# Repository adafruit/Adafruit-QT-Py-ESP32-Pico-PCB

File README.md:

## Adafruit QT Py ESP32 Pico - WiFi Dev Board with STEMMA QT

<a href="http://www.adafruit.com/products/5395"><br/>
Click here to purchase one from the Adafruit shop</a>

PCB files for the Adafruit QT Py ESP32 Pico.

Format is EagleCAD schematic and board layout
* https://www.adafruit.com/product/5395

### Description

This dev board is like when you're watching a super-hero movie and the protagonist shows up in a totally amazing costume in the third act and you're like 'OMG! That's the hero and they're here to kick some serious butt!" but in this case its a microcontroller.

This QT Py board is a thumbnail-sized PCB that features the ESP32 Pico V3 02, an all-in-one chip that has an ESP32 chip with dual-core 240MHz Tensilica processor, WiFi and Bluetooth classic + BLE, adds a bunch of required passives and oscillator, 8 MB of Flash memory and 2 MB of PSRAM. We add a USB to serial converter chip, some more passives, an antenna, USB C, buttons, NeoPixel and QT connector to outfit this super-hero chip for any task you want to throw it at.

At the core of ESP32-PICO-V3-02 is the ESP32 (ECO V3) chip, which is a single 2.4 GHz Wi-Fi and Bluetooth combo chip designed with TSMC’s 40 nm low-power technology. ESP32-PICO-V3-02 integrates all peripheral components seamlessly, including a crystal oscillator, flash, PSRAM, filter capacitors, and RF matching links in one single package. This makes it perfect for stuffing into such a small space as the QT Py.

Please note the QT Py ESP32 Pico does not have native USB support - instead there's a USB to serial converter chip. This means it cannot act like a USB keyboard or mouse - but it does have BLE and BT classic so you could  wireless.

OLEDs! Inertial Measurement Units! Sensors a-plenty. All plug-and-play thanks to the innovative chainable design: SparkFun Qwiic-compatible STEMMA QT connectors for the I2C bus so you don't even need to solder! Just plug in a compatible cable and attach it to your MCU of choice, and you’re ready to load up some software and measure some light. Seeed Grove I2C boards will also work with this adapter cable.

Pinout and shape are Seeed Xiao compatible, with castellated pads. In addition to the QT connector, we also added an RGB NeoPixel (with controllable power pin to allow for ultra-low-power usage), a reset button (great for restarting your program or entering the bootloader), and a button on GPIO 0 for entering the ROM bootloader or for user input

Runs Arduino like a dream, or use the ESP IDF for more control over your projects.

* Same size, form-factor, and pin-out as Seeed Xiao
* USB Type C connector - If you have only Micro B cables, this adapter will come in handy!
* ESP32 V2 03 Dual Core 240MHz Xtensa processor - the ESP32 you know and love, with the latest engineering fixes. Massive user base and thousands of existing projects and libraries to use.
* WiFi, Bluetooth LE and Classic for any IoT project usage
* 8 MB Flash & 2 MB PSRAM
* USB to Serial converter built in with high speed UART for debugging and uploading.
* Can be used with Arduino IDE or MicroPython
* Built-in RGB NeoPixel LED with power control to reduce quiescent power in deep sleep
* Battery input pads on underside with diode protection for external battery packs up to 6V input
* 13 GPIO pins:
  * 11 on breakout pads, 2 more on QT connector
  * 10 x 12-bit analog inputs
  * Dual 8-bit analog output DACs on A0/A1
  * PWM outputs on any pin
  * Two I2C ports, one on the breakout pads, and another with STEMMA QT plug-n-play connector
  * Hardware UART in addition to the USB-serial UART
  * Hardware SPI on the high speed SPI peripheral pins
  * Hardware I2S on any pins
  * 8 x Capacitive Touch with no additional components required
* 3.3V regulator with 600mA peak output
* Light sleep at 4mA, deep sleep at ~70uA
* Reset switch for starting your project code over, boot 0 button for entering bootloader mode or for user reading
* Really really small

### License

Adafruit invests time and resources providing this open source design, please support Adafruit and open-source hardware by purchasing products from [Adafruit](https://www.adafruit.com)!

Designed by Limor Fried/Ladyada for Adafruit Industries.

Creative Commons Attribution/Share-Alike, all text above must be included in any redistribution. 
See license.txt for additional details.

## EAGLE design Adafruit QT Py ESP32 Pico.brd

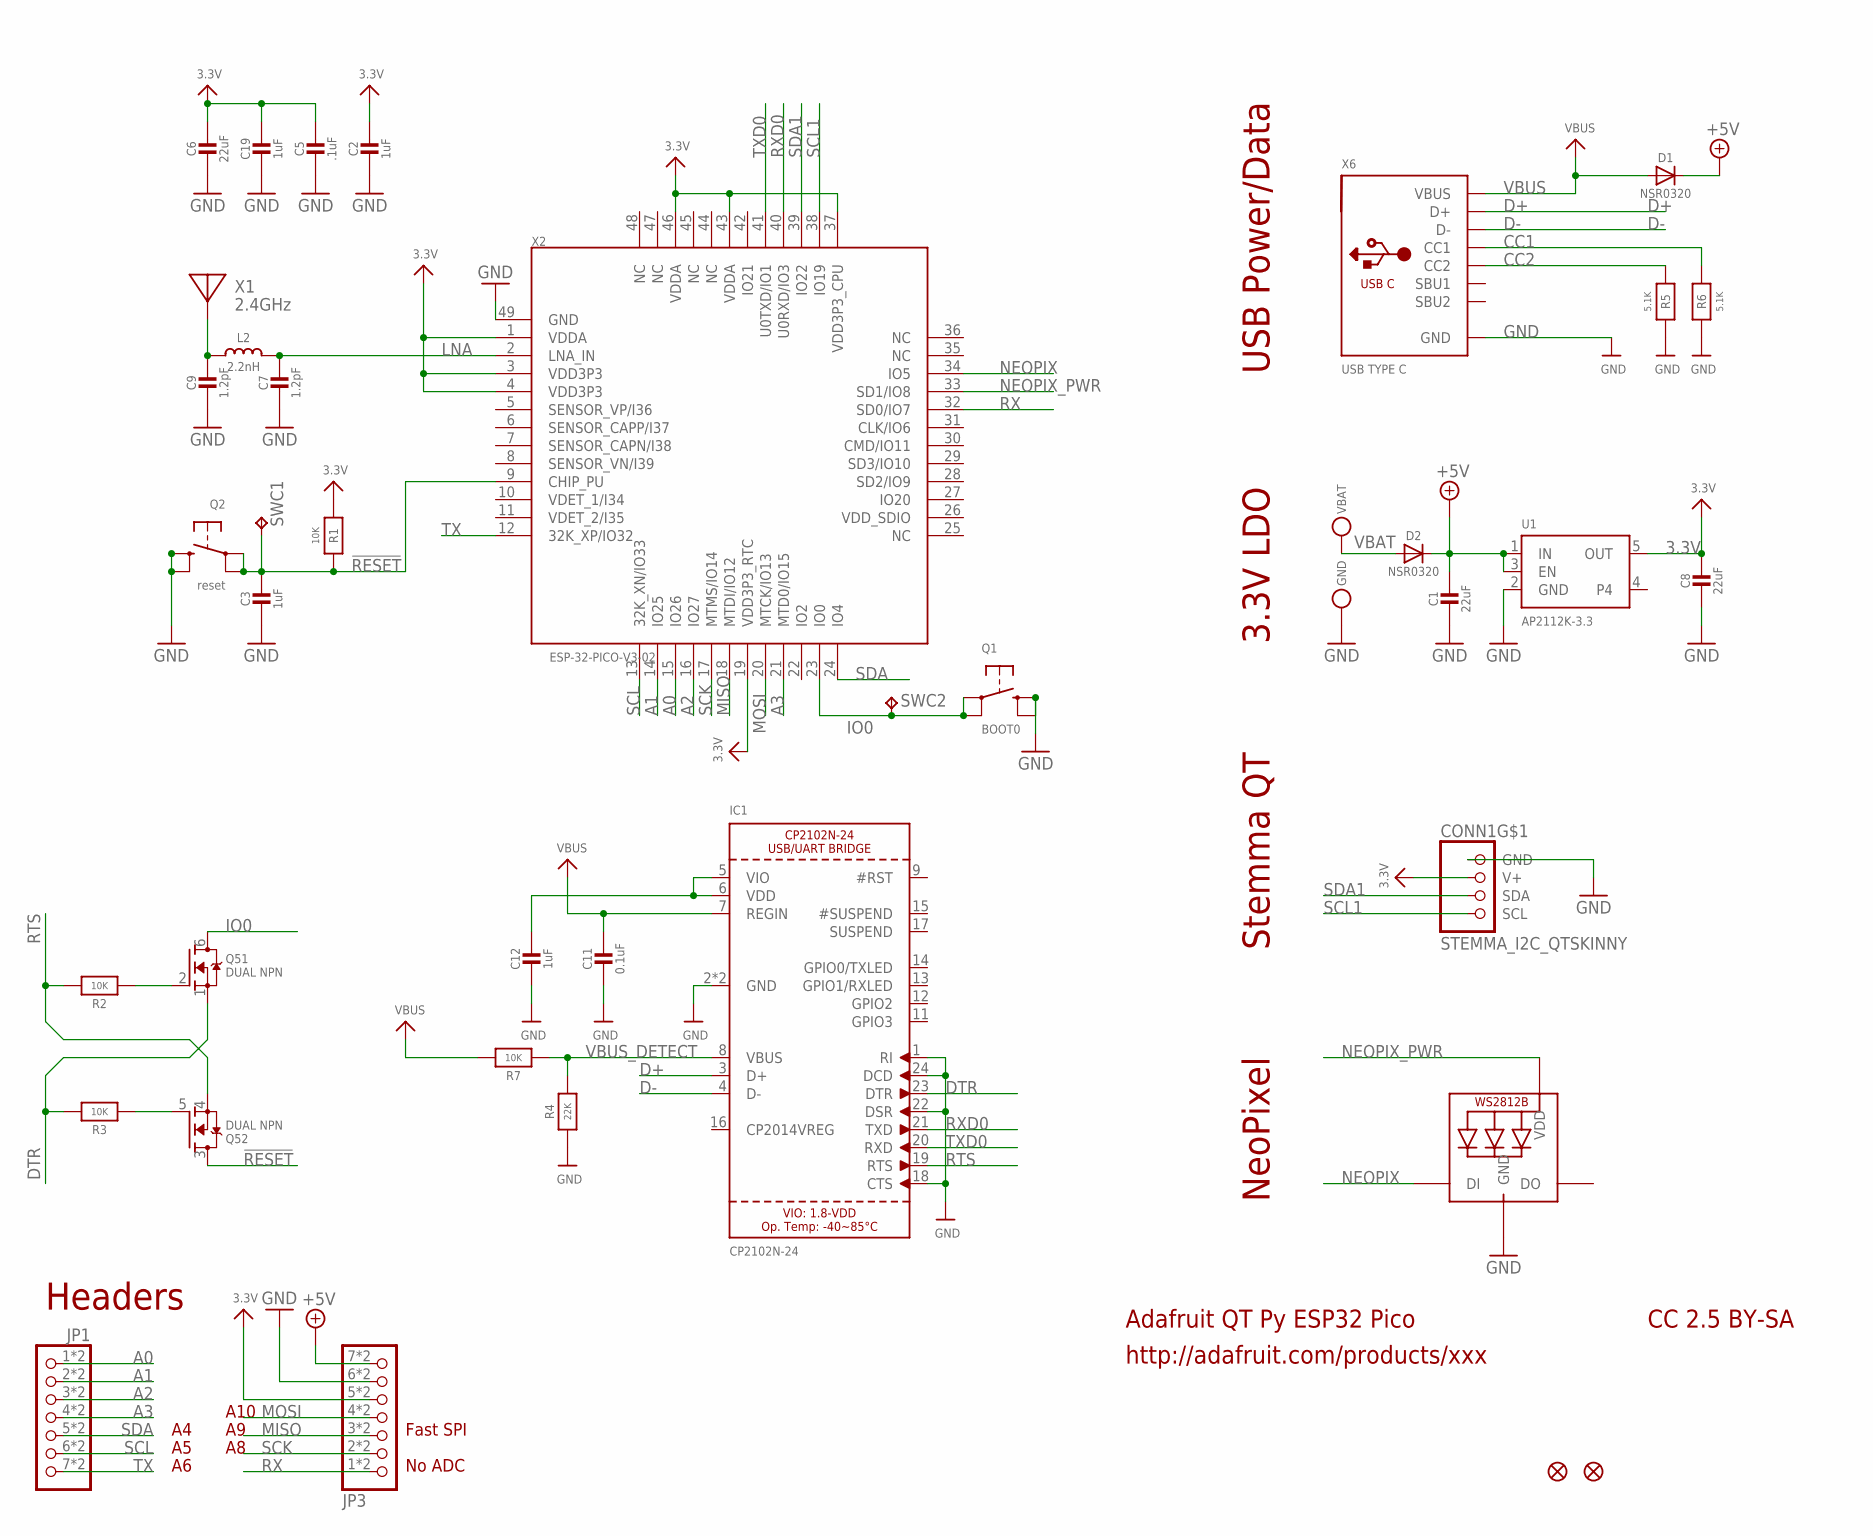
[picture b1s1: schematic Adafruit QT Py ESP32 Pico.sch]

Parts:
C1, C6, C8: 22uF; 0805-NO
C2, C3, C12: 1uF; _0402NO
C5: .1uF; _0402NO
C7, C9: 1.2pF; _0402NO
C11: 0.1uF; _0402NO
C19: 1uF; 0603-NO_WIDE
CONN1: STEMMA_I2C_QTSKINNY; JST_SH4_SKINNY
D1, D2: NSR0320; SOD-323_MINI
GND: TESTPOINT_MINUS; TESTPOINT_MINUS_1X3MM
IC1: CP2102N-24; QFN24_4MM_SMSC
JP1, JP3: HEADER-1X7_CASTEL; 1X07_CASTEL
L2: 2.2nH; _0402
LED1: WS2812B_SK6805_1515; SK6805_1515
Q1: BOOT0; BTN_KMR2_4.6X2.8
Q2: reset; BTN_KMR2_4.6X2.8
Q5: DUAL NPN; SOT363
R1, R2, R3, R7: 10K; _0402NO
R4: 22K; _0402NO
R5, R6: 5.1K; _0402NO
SWC1, SWC2: TPB1,27; B1,27
U1: AP2112K-3.3; SOT23-5
U$6, U$8: FIDUCIAL_1MM
VBAT: TESTPOINT_PLUS13; TESTPOINT_PLUS_1X3MM
X1: 2.4GHz; ANT_2450AT18B100
X2: ESP-32-PICO-V3-02; QFN48_7X7
X6: USB TYPE C; USB_C_CUSB31-CFM2AX-01-X

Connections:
3.3V: C2.1, C5.1, C6.1, C8.1, C19.1, CONN1.2 (V+), JP3.5, JP3.5C (5), R1.1, U1.5 (OUT), X2.1 (VDDA), X2.3 (VDD3P3), X2.4 (VDD3P3), X2.19 (VDD3P3_RTC), X2.37 (VDD3P3_CPU), X2.43 (VDDA), X2.46 (VDDA)
!RESET: C3.1, Q2.A, Q2.A' (P1), Q5.3 (D), R1.2, SWC1.TP, X2.9 (CHIP_PU)
+5V: C1.1, D1.C, D2.C, JP3.7, JP3.7C (7), U1.1 (IN), U1.3 (EN)
A0: JP1.1, JP1.1C (1), X2.15 (IO26)
A1: JP1.2, JP1.2C (2), X2.14 (IO25)
A2: JP1.3, JP1.3C (3), X2.16 (IO27)
A3: JP1.4, JP1.4C (4), X2.21 (MTD0/IO15)
CC1: R6.2, X6.A5 (CC1)
CC2: R5.2, X6.B5 (CC2)
D+: IC1.3 (D+), X6.A6 (D+), X6.B6 (D+)
D-: IC1.4 (D-), X6.A7 (D-), X6.B7 (D-)
DTR: IC1.23 (DTR), Q5.1 (S), R3.2
GND: C1.2, C2.2, C3.2, C5.2, C6.2, C7.2, C8.2, C9.2, C11.2, C12.2, C19.2, CONN1.1 (GND), GND.P$1, IC1.1 (RI), IC1.2 (GND), IC1.18 (CTS), IC1.22 (DSR), IC1.24 (DCD), IC1.THERM (GND), JP3.6, JP3.6C (6), LED1.4 (GND), Q1.B (S), Q1.B' (S1), Q2.B (S), Q2.B' (S1), R4.1, R5.1, R6.1, U1.2 (GND), X2.49 (GND), X6.A1B12 (GND), X6.B1A12 (GND)
IO0: Q1.A, Q1.A' (P1), Q5.6 (D), SWC2.TP, X2.23 (IO0)
LNA: C7.1, L2.2, X2.2 (LNA_IN)
MISO: JP3.3, JP3.3C (3), X2.18 (MTDI/IO12)
MOSI: JP3.4, JP3.4C (4), X2.20 (MTCK/IO13)
unnamed: C12.1, IC1.5 (VIO), IC1.6 (VDD)
unnamed: C9.1, L2.1, X1.FP
unnamed: Q5.5 (G), R3.1
unnamed: Q5.2 (G), R2.1
NEOPIX: LED1.1 (DI), X2.34 (IO5)
NEOPIX_PWR: LED1.2 (VDD), X2.33 (SD1/IO8)
RTS: IC1.19 (RTS), Q5.4 (S), R2.2
RX: JP3.1, JP3.1C (1), X2.32 (SD0/IO7)
RXD0: IC1.21 (TXD), X2.40 (U0RXD/IO3)
SCK: JP3.2, JP3.2C (2), X2.17 (MTMS/IO14)
SCL: JP1.6, JP1.6C (6), X2.13 (32K_XN/IO33)
SCL1: CONN1.4 (SCL), X2.38 (IO19)
SDA: JP1.5, JP1.5C (5), X2.24 (IO4)
SDA1: CONN1.3 (SDA), X2.39 (IO22)
TX: JP1.7, JP1.7C (7), X2.12 (32K_XP/IO32)
TXD0: IC1.20 (RXD), X2.41 (U0TXD/IO1)
VBAT: D2.A, VBAT.P$1
VBUS: C11.1, D1.A, IC1.7 (REGIN), R7.2, X6.A4B9 (VBUS), X6.B4A9 (VBUS)
VBUS_DETECT: IC1.8 (VBUS), R4.2, R7.1

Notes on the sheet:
Adafruit QT Py ESP32 Pico
http://adafruit.com/products/xxx
CC 2.5 BY-SA
NeoPixel
Stemma QT
3.3V LDO
USB Power/Data
Headers
Fast SPI
No ADC
A10

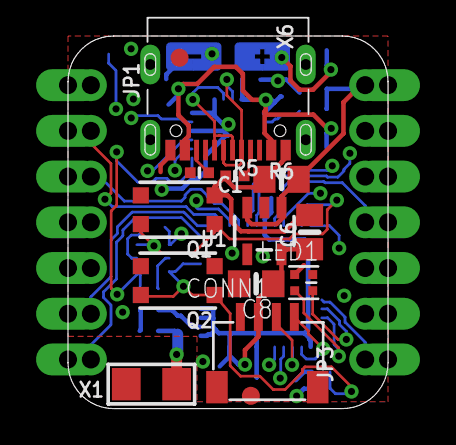
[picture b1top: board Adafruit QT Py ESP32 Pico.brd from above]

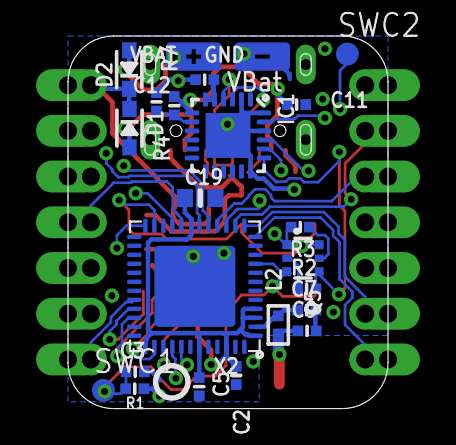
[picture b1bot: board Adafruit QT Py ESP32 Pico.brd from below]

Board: 4 copper layers, 17.8 x 20.7 mm, 42 parts (25 on the bottom side), 36 nets.

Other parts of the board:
U$3: QTPY_ESP32_BOT
U$12: PCBFEAT-REV-040
U$22: QTPY_ESP32_TOP

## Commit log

2022-05-26 Add PrettyPins.
2022-05-27 Add factory reset file.
2022-06-07 Add PrettyPins

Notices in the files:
parts and their libraries:
microbuilder: This work is placed in the public domain, and may be freely used for commercial and non-commercial work with the following conditions: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
